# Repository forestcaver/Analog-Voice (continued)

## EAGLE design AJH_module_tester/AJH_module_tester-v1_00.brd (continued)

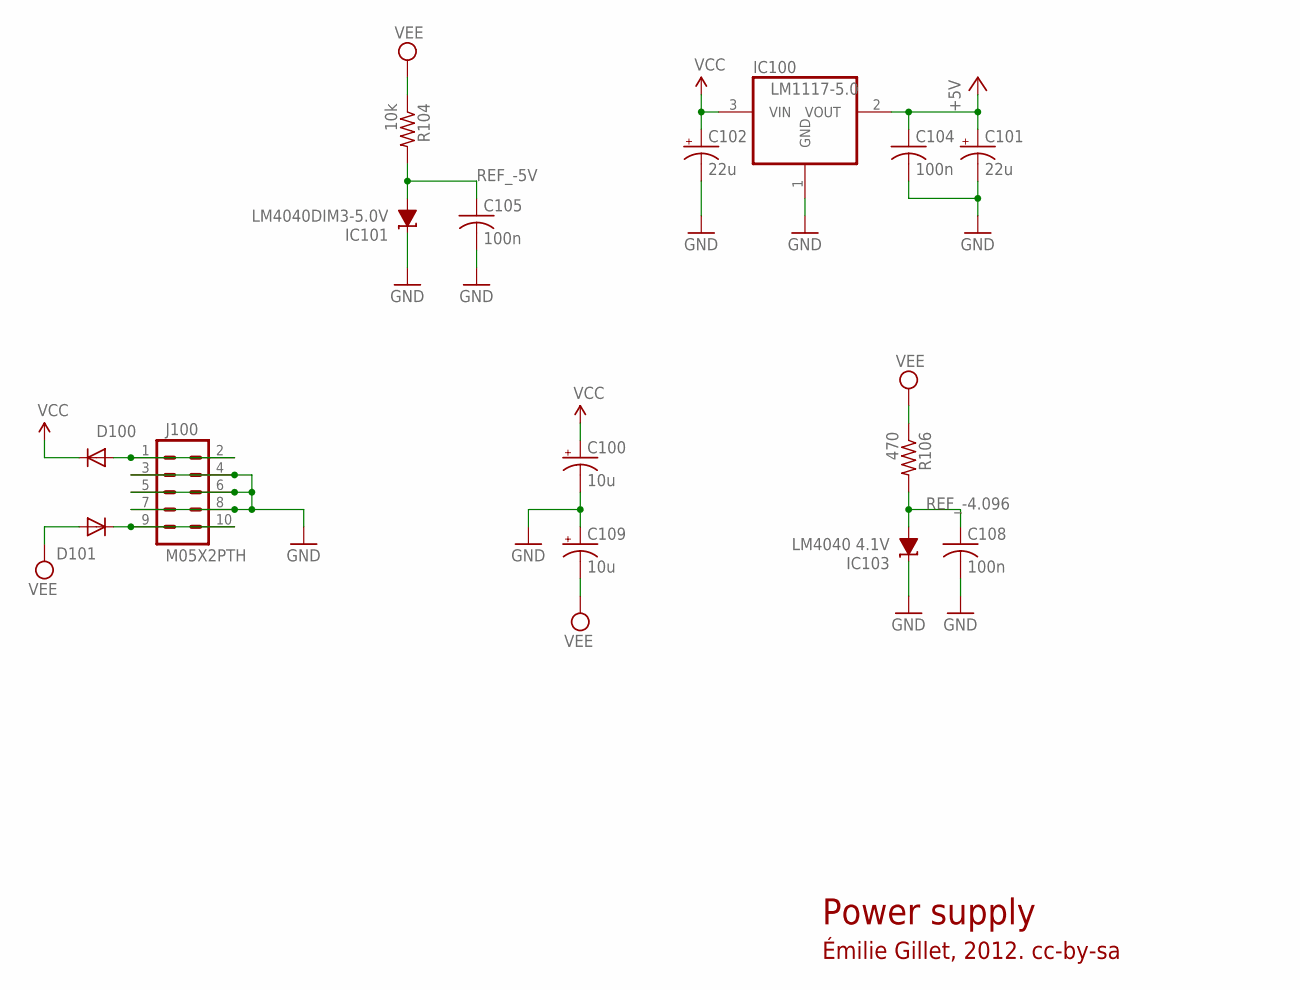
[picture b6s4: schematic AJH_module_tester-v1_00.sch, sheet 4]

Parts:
C100, C109: 10u; PANASONIC_B
C101, C102: 22u; PANASONIC_C
C104, C105, C108: 100n; C0603
D100, D101: 1N5819HW; SOD123
IC100: LM1117-5.0; SOT223
IC101: LM4040DIM3-5.0V; DBZ_R-PDSO-G3
IC103: LM4040 4.1V; DBZ_R-PDSO-G3
J100: M05X2PTH; AVR_ICSP
R104: 10k; R0603
R106: 470; R0603

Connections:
+5V: C101.+, C104.1, IC100.2 (VOUT); also elsewhere on the board
GND: C100.-, C101.-, C102.-, C104.2, C105.2, C108.2, C109.+, IC100.1 (GND), IC101.1 (C), IC103.1 (C), J100.3, J100.4, J100.5, J100.6, J100.7, J100.8; also elsewhere on the board
unnamed: D100.A, J100.1, J100.2
unnamed: D101.C, J100.9, J100.10
REF_-4.096: C108.1, IC103.2 (A), R106.2; also elsewhere on the board
REF_-5V: C105.1, IC101.2 (A), R104.2; also elsewhere on the board
VCC: C100.+, C102.+, D100.C, IC100.3 (VIN); also elsewhere on the board
VEE: C109.-, D101.A, R104.1, R106.1; also elsewhere on the board

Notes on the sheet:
Power supply
Émilie Gillet, 2012. cc-by-sa

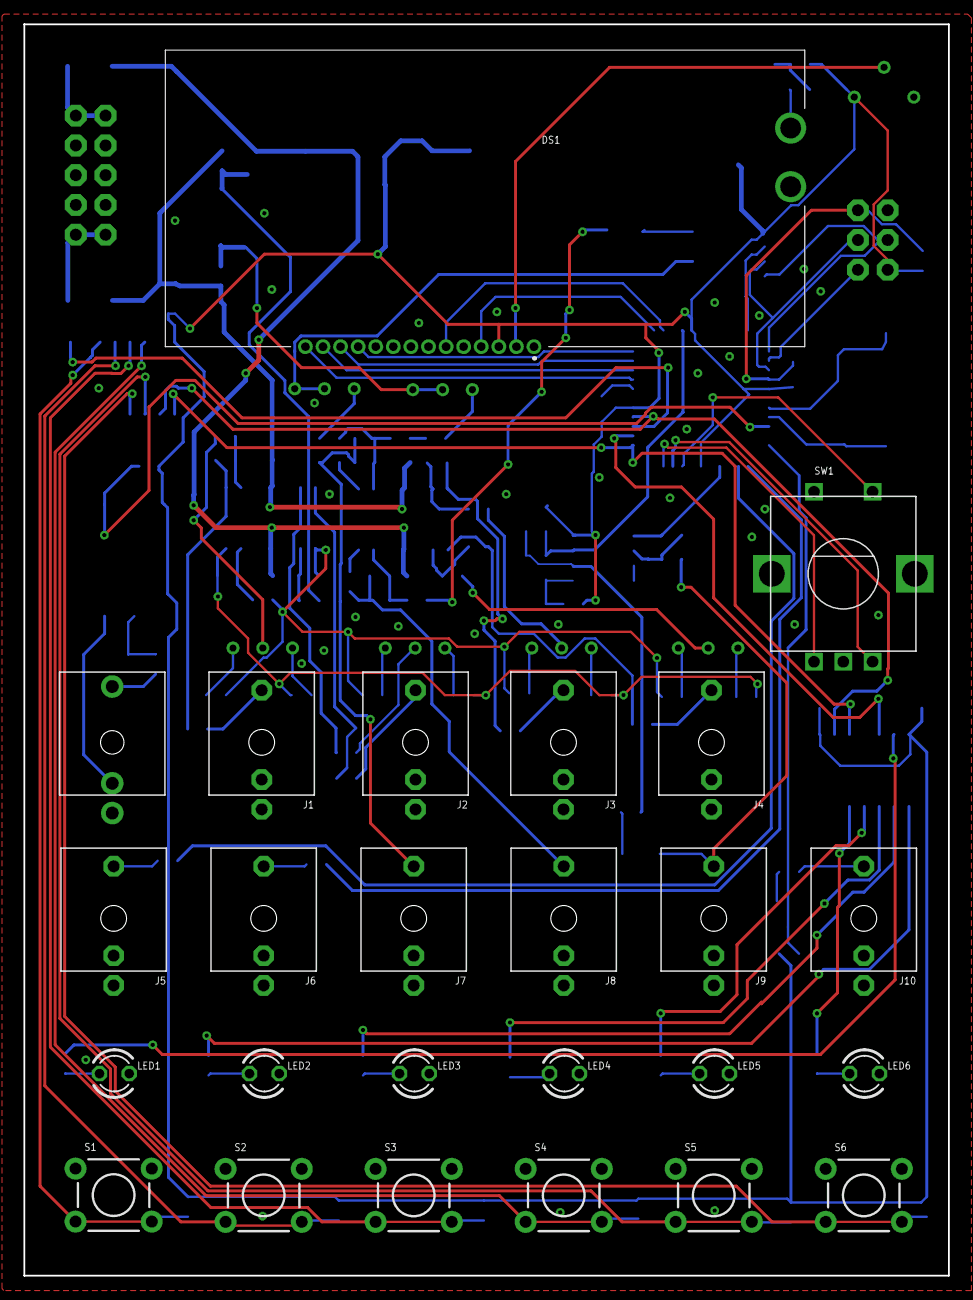
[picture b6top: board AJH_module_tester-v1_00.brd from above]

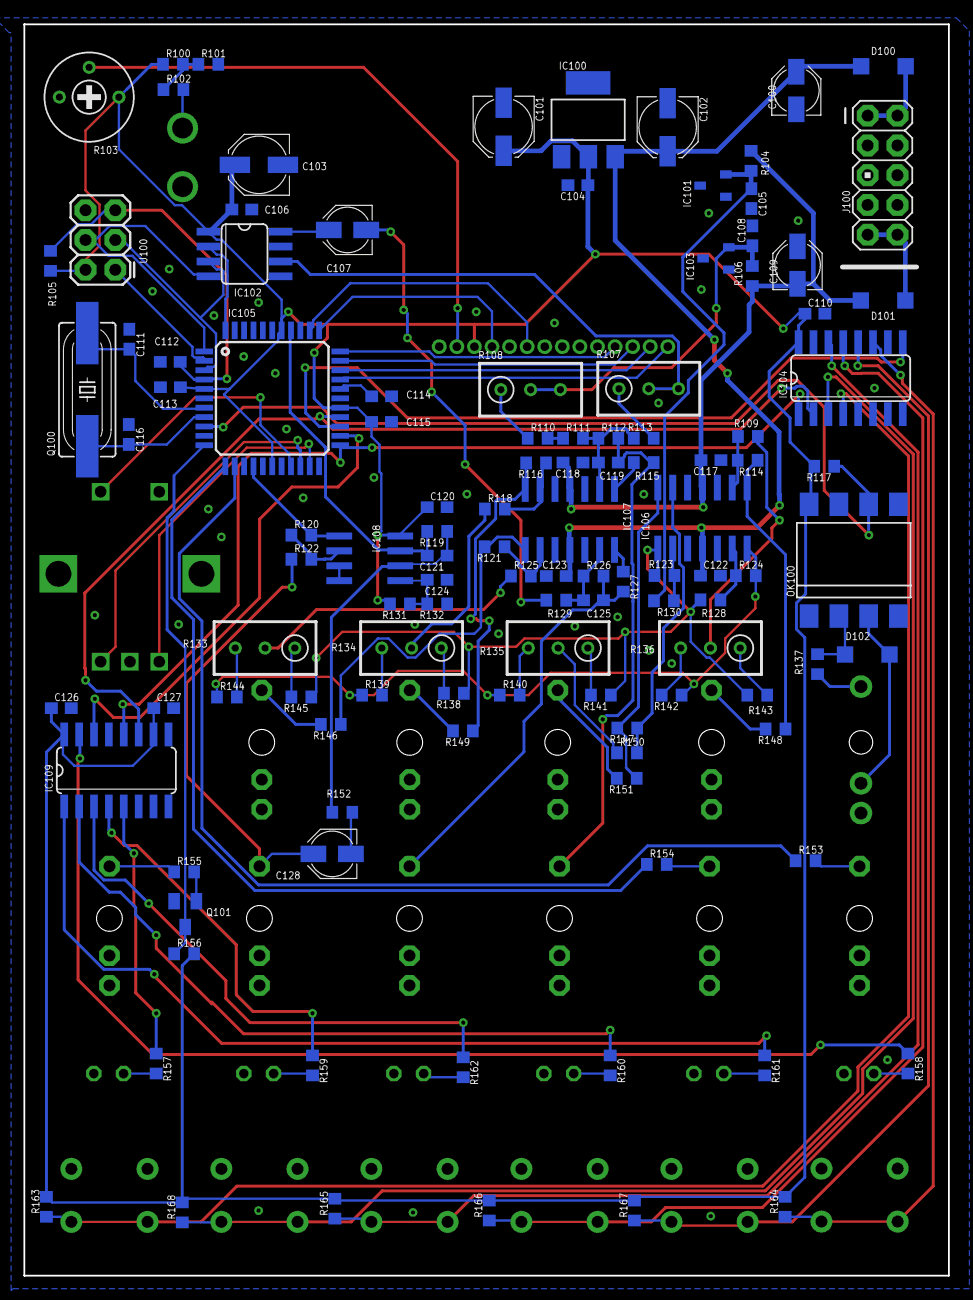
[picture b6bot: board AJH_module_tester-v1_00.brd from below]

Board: 2 copper layers, 78.9 x 106.8 mm, 141 parts (116 on the bottom side), 108 nets.

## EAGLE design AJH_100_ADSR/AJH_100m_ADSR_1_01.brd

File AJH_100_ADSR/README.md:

# A100 ADSR

Built and tested

CC-BY-NC-SA 4.0

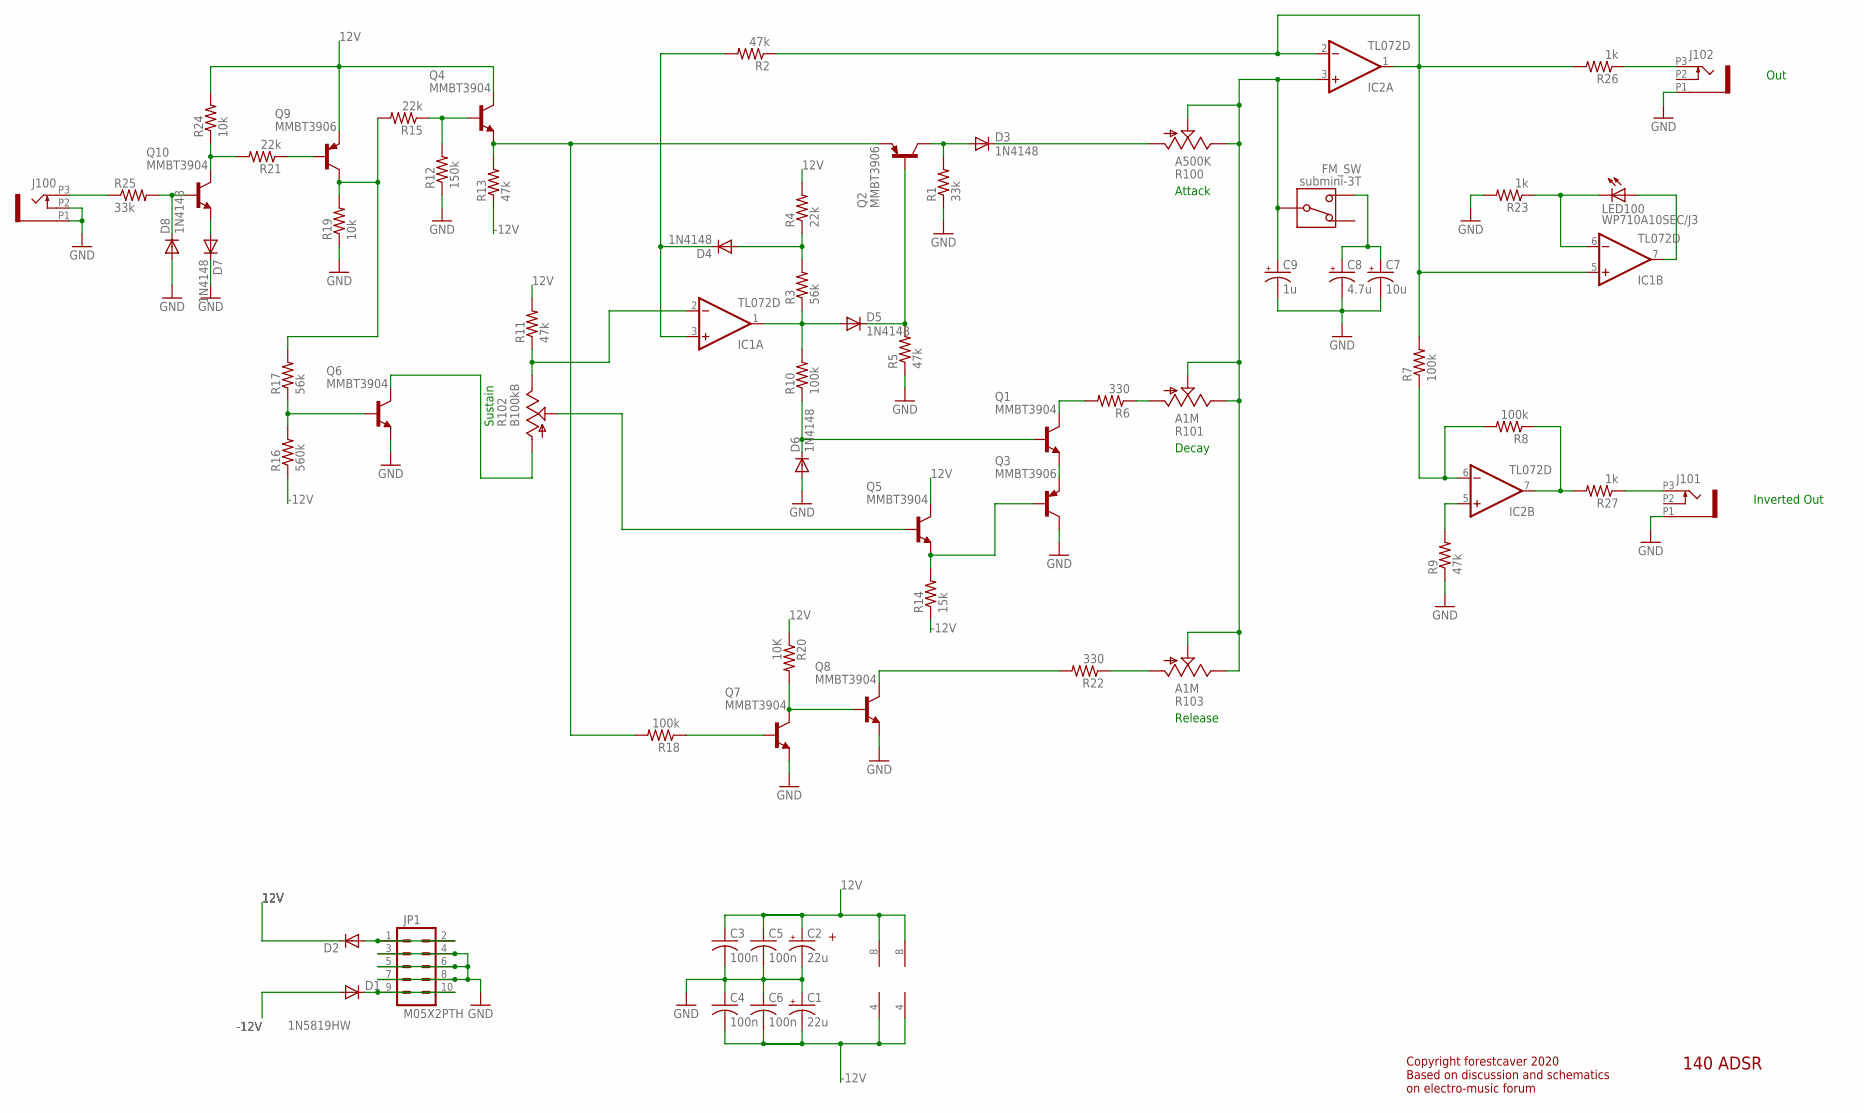
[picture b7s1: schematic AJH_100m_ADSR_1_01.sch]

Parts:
C1, C2: 22u; PANASONIC_B
C3, C4, C5, C6: 100n; C0603
C7: 10u; PANASONIC_B
C8: 4.7u; PANASONIC_B
C9: 1u; PANASONIC_B
D1, D2: 1N5819HW; SOD123
D3, D4, D5, D6, D7, D8: 1N4148; SOD323-W
FM_SW: submini-3T; SPDT-SUB
IC1, IC2: TL072D; SO08
J100, J101, J102: PJ301_THONKICONN6; WQP_PJ_301M6
JP1: M05X2PTH; AVR_ICSP
LED100: WP710A10SEC/J3; LED3MM
Q1, Q4, Q5, Q6, Q7, Q8, Q10: MMBT3904; SOT23-BEC
Q2, Q3, Q9: MMBT3906; SOT23-BEC
R1, R25: 33k; R0603
R2, R5, R9, R11, R13: 47k; R0603
R3, R17: 56k; R0603
R4, R15, R21: 22k; R0603
R6, R22: 330; R0603
R7, R8, R10, R18: 100k; R0603
R12: 150k; R0603
R14: 15k; R0603
R16: 560k; R0603
R19, R24: 10k; R0603
R20: 10K; R0603
R23, R26, R27: 1k; R0603
R100: A500K; ALPS_POT_VERTICAL
R101, R103: A1M; ALPS_POT_VERTICAL
R102: B100kB; ALPS_POT_VERTICAL

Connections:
12V: C2.+, C3.1, C5.1, D2.C, IC1.8 (V+), IC2.8 (V+), Q4.C, Q5.C, Q9.E, R4.2, R11.2, R20.1, R24.2
-12V: C1.-, C4.2, C6.2, D1.A, IC1.4 (V-), IC2.4 (V-), R13.1, R14.1, R16.1
GND: C1.+, C2.-, C3.2, C4.1, C5.2, C6.1, C7.-, C8.-, C9.-, D6.A, D7.C, D8.A, J100.P1 (1), J100.P2 (2), J101.P1 (1), J102.P1 (1), JP1.3, JP1.4, JP1.5, JP1.6, JP1.7, JP1.8, Q3.C, Q6.E, Q7.E, Q8.E, R1.1, R5.1, R9.1, R12.1, R19.1, R23.2
unnamed: IC1.6 (-IN), LED100.K (C), R23.1
unnamed: IC2.6 (-IN), R7.1, R8.2
unnamed: D4.A, R3.2, R4.1
unnamed: IC1.7 (OUT), LED100.A
unnamed: D3.C, R100.P$3 (A)
unnamed: D2.A, JP1.1, JP1.2
unnamed: R6.1, R101.P$3 (A)
unnamed: R22.1, R103.P$3 (A)
unnamed: C7.+, C8.+, FM_SW.P$1
unnamed: IC1.5 (+IN), IC2.1 (OUT), IC2.2 (-IN), R2.1, R7.2, R26.2
unnamed: J102.P3 (3), R26.1
unnamed: IC2.7 (OUT), R8.1, R27.2
unnamed: J100.P3 (3), R25.1
unnamed: IC2.5 (+IN), R9.2
unnamed: D8.C, Q10.B, R25.2
unnamed: D7.A, Q10.E
unnamed: Q10.C, R21.2, R24.1
unnamed: Q9.B, R21.1
unnamed: D1.C, JP1.9, JP1.10
unnamed: Q9.C, R15.2, R17.2, R19.2
unnamed: Q2.E, Q4.E, R13.2, R18.2
unnamed: Q4.B, R12.2, R15.1
unnamed: Q6.C, R102.P$3 (A)
unnamed: Q6.B, R16.2, R17.1
unnamed: IC1.2 (-IN), R11.1, R102.P$1 (E)
unnamed: D4.C, IC1.3 (+IN), R2.2
unnamed: Q5.B, R102.P$2 (S)
unnamed: D3.A, Q2.C, R1.2
unnamed: D5.C, Q2.B, R5.2
unnamed: D5.A, IC1.1 (OUT), R3.1, R10.2
unnamed: D6.C, Q1.B, R10.1
unnamed: Q1.E, Q3.E
unnamed: Q1.C, R6.2
unnamed: Q3.B, Q5.E, R14.2
unnamed: C9.+, FM_SW.P$2, IC2.3 (+IN), R100.P$1 (E), R100.P$2 (S), R101.P$1 (E), R101.P$2 (S), R103.P$1 (E), R103.P$2 (S)
unnamed: J101.P3 (3), R27.1
unnamed: Q7.C, Q8.B, R20.2
unnamed: Q8.C, R22.2
unnamed: Q7.B, R18.1

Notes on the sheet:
Sustain
Release
Decay
Attack
Out
Inverted Out
Copyright forestcaver 2020 Based on discussion and schematics on electro-music forum
140 ADSR

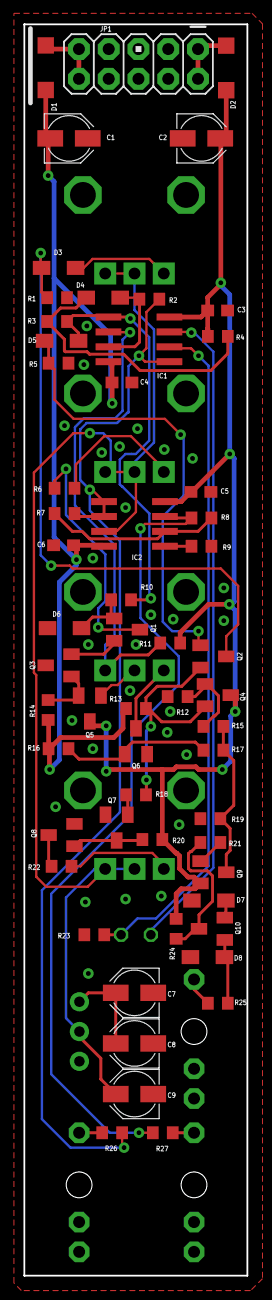
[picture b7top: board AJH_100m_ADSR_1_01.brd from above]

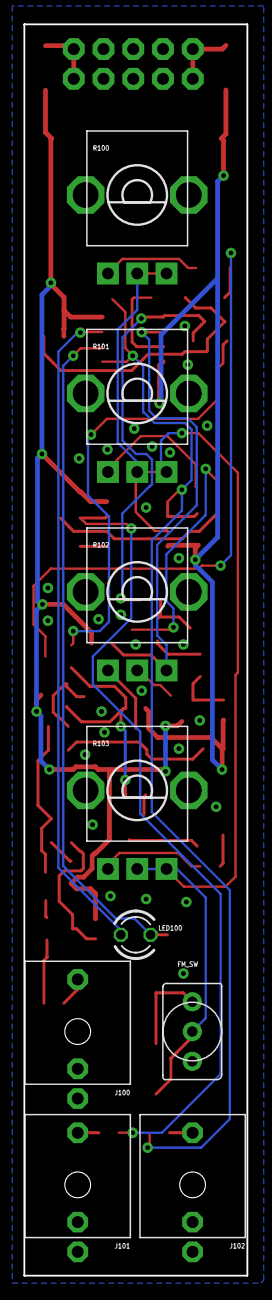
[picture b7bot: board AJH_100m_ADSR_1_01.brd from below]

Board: 2 copper layers, 19.0 x 106.8 mm, 66 parts (9 on the bottom side), 42 nets.

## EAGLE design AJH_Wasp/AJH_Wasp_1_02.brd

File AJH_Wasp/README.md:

# Wasp filter

Built and tested

Note that the switch needs to have the legs extended with some eg resistor legs to be flush with the panel - I mounted mine on a header....

Also, consider increasing R25 to 100k to keep the level of the distortion signal the same as the non-distorted signal

CC-BY-NC-SA 4.0

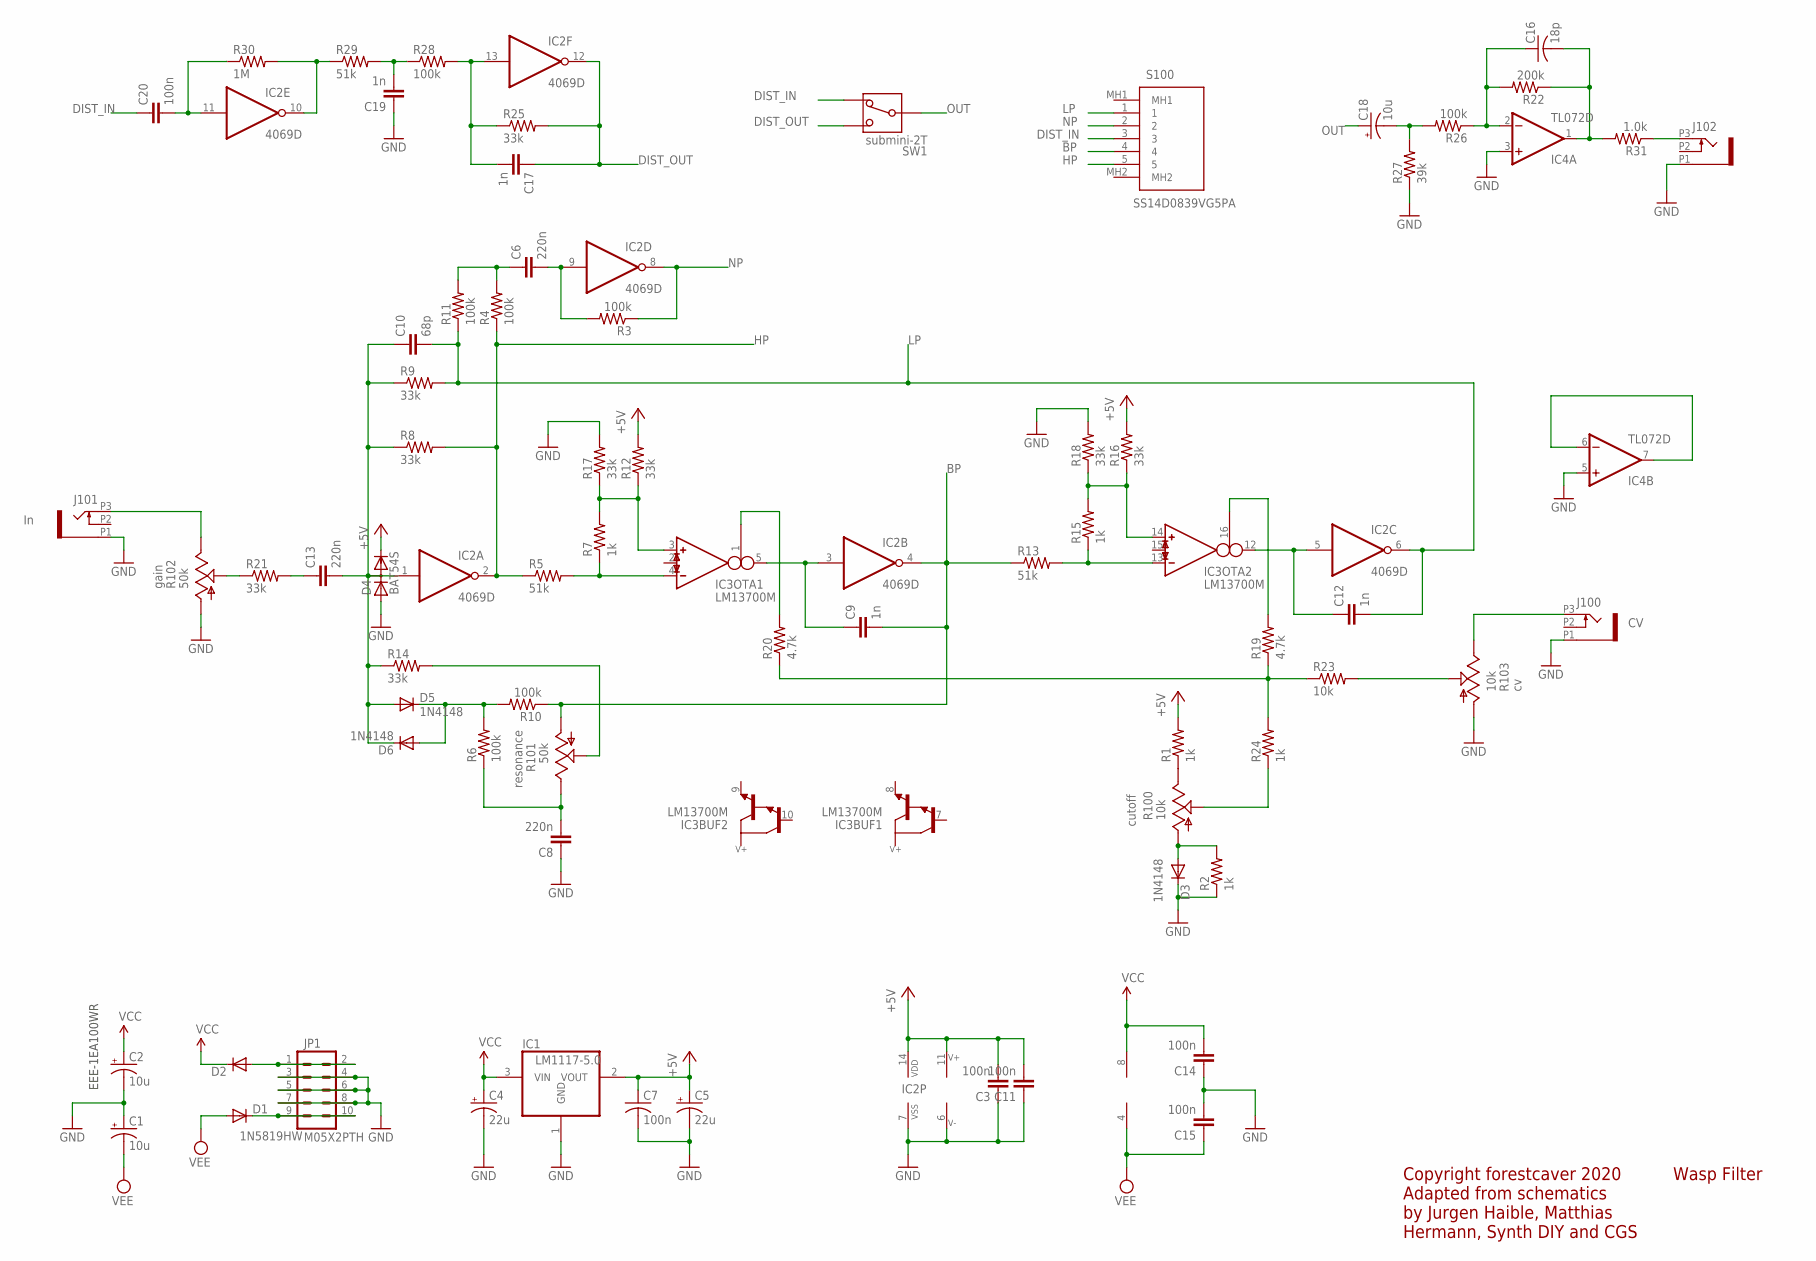
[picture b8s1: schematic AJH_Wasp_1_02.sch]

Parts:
C1, C2, C18: 10u; PANASONIC_B
C3, C7, C11, C14, C15, C20: 100n; C0603
C4, C5: 22u; PANASONIC_C
C6, C8, C13: 220n; C0603
C9, C12, C17, C19: 1n; C0603
C10: 68p; C0603
C16: 18p; C0603
D1, D2: 1N5819HW; SOD123
D3, D5, D6: 1N4148; SOD523
D4: BAT54S; SOT23
IC1: LM1117-5.0; SOT223
IC2: 4069D; SO14
IC3: LM13700M; SO16
IC4: TL072D; SO08
J100, J101: PJ301_THONKICONN8; WQP_PJ_301M8
J102: PJ301_THONKICONN6; WQP_PJ_301M6
JP1: M05X2PTH; AVR_ICSP
R1, R2, R7, R15, R24: 1k; R0603
R3, R4, R6, R10, R11, R26, R28: 100k; R0603
R5, R13, R29: 51k; R0603
R8, R9, R12, R14, R16, R17, R18, R21, R25: 33k; R0603
R19, R20: 4.7k; R0603
R22: 200k; R0603
R23: 10k; R0603
R27: 39k; R0603
R30: 1M; R0603
R31: 1.0k; R0603
R100, R103: 10k; ALPS_POT_VERTICAL_PS
R101, R102: 50k; ALPS_POT_VERTICAL_PS
S100: SS14D0839VG5PA
SW1: submini-2T; SPDT-SUB

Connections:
+5V: C3.2, C5.+, C7.1, C11.2, D4.2 (C), IC1.2 (VOUT), IC2.14 (VDD), IC3.11 (V+), R1.2, R12.2, R16.2
BP: C9.2, IC2.4 (O), R10.1, R13.1, R101.P$3 (A), S100.4
DIST_IN: C20.1, S100.3, SW1.P$3
DIST_OUT: C17.1, IC2.12 (O), R25.2, SW1.P$1
GND: C1.+, C2.-, C3.1, C4.-, C5.-, C7.2, C8.1, C11.1, C14.1, C15.2, C19.1, D3.C, D4.1 (A), IC1.1 (GND), IC2.7 (VSS), IC3.6 (V-), IC4.3 (+IN), IC4.5 (+IN), J100.P1 (1), J101.P1 (1), J102.P1 (1), JP1.3, JP1.4, JP1.5, JP1.6, JP1.7, JP1.8, R2.1, R17.2, R18.2, R27.1, R102.P$3 (A), R103.P$3 (A)
HP: IC2.2 (O), R4.1, R5.1, R8.2, S100.5
LP: C10.2, C12.2, IC2.6 (O), R9.2, R11.1, S100.1
unnamed: J101.P3 (3), R102.P$1 (E)
unnamed: R21.1, R102.P$2 (S)
unnamed: C13.1, R21.2
unnamed: C10.1, C13.2, D4.3 (AC), D5.A, D6.C, IC2.1 (I), R8.1, R9.1, R14.1
unnamed: IC3.14 (IN_P), R15.2, R16.1, R18.1
unnamed: D2.A, JP1.1, JP1.2
unnamed: IC3.1 (I_BIAS), R20.2
unnamed: C6.2, IC2.9 (I), R3.2
unnamed: C6.1, R4.2, R11.2
unnamed: D5.C, D6.A, R6.2, R10.2
unnamed: IC3.13 (IN_N), R13.2, R15.1
unnamed: C8.2, R6.1, R101.P$1 (E)
unnamed: R14.2, R101.P$2 (S)
unnamed: IC3.3 (IN_P), R7.2, R12.1, R17.1
unnamed: IC3.4 (IN_N), R5.2, R7.1
unnamed: C9.1, IC2.3 (I), IC3.5 (OUT)
unnamed: IC3.16 (I_BIAS), R19.2
unnamed: R19.1, R20.1, R23.1, R24.2
unnamed: C12.1, IC2.5 (I), IC3.12 (OUT)
unnamed: D1.C, JP1.9, JP1.10
unnamed: R23.2, R103.P$2 (S)
unnamed: R1.1, R100.P$1 (E)
unnamed: D3.A, R2.2, R100.P$3 (A)
unnamed: R24.1, R100.P$2 (S)
unnamed: C20.2, IC2.11 (I), R30.1
unnamed: IC2.10 (O), R29.1, R30.2
unnamed: C19.2, R28.1, R29.2
unnamed: C17.2, IC2.13 (I), R25.1, R28.2
unnamed: J100.P3 (3), R103.P$1 (E)
unnamed: IC4.6 (-IN), IC4.7 (OUT)
unnamed: C18.-, R26.2, R27.2
unnamed: C16.1, IC4.2 (-IN), R22.2, R26.1
unnamed: C16.2, IC4.1 (OUT), R22.1, R31.2
NP: IC2.8 (O), R3.1, S100.2
OUT: C18.+, SW1.P$2
ROUT_JACK1: J102.P3 (3), R31.1
VCC: C2.+, C4.+, C14.2, D2.C, IC1.3 (VIN), IC4.8 (V+)
VEE: C1.-, C15.1, D1.A, IC4.4 (V-)

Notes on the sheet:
EEE-1EA100WR
Wasp Filter
Copyright forestcaver 2020 Adapted from schematics by Jurgen Haible, Matthias Hermann, Synth DIY and CGS

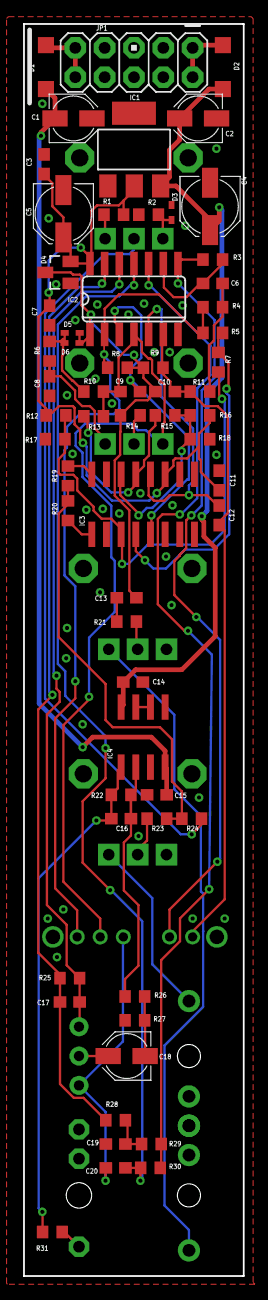
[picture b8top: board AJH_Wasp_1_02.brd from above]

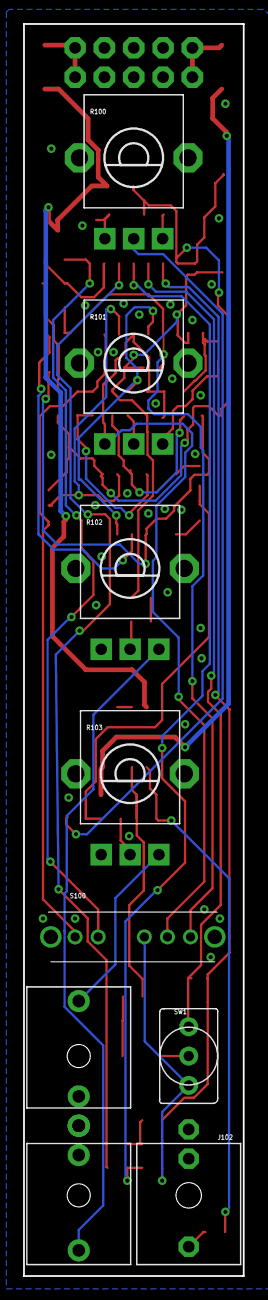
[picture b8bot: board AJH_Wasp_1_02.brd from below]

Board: 2 copper layers, 19.0 x 108.4 mm, 71 parts (9 on the bottom side), 45 nets.

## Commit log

2020-01-19 lpg image
2020-05-01 Module tester module
2020-05-01 2v vca
2020-05-01 readmes
2020-05-01 move images
2020-05-01 More modules uploaded
2020-05-13 Panels for 4 new modules
2020-06-20 Wasp update v1.02 - correct reversed Q pot
2020-06-20 Add Wasp gerber
2020-06-21 AJH_ssi2144 corrections to prototype
2020-06-21 Updated a100 adsr with correct pot direction
2020-07-04 Update module tester
2020-07-06 Update module tester panel
2020-07-09 Updated footprint for vactrol on lpg
2020-08-04 Fix gate input (pulldown)
2020-08-23 Notes on module tester module and matrix mixer
2020-09-27 Add 2B_VCA, add some comments on ssi2144 schematic
2020-09-27 2b image
2020-09-27 Add through hole tempco to ssi2144
2020-09-27 housekeeping
2021-03-03 New module images
2021-03-03 Added text for new modules in readme
2021-03-04 Typo on ssi2144 schematic comments
2021-03-21 Add matrix mixer
2022-08-29 Update README.md
    Update 2B
    error
2023-07-03 Add 'red strip' mark
